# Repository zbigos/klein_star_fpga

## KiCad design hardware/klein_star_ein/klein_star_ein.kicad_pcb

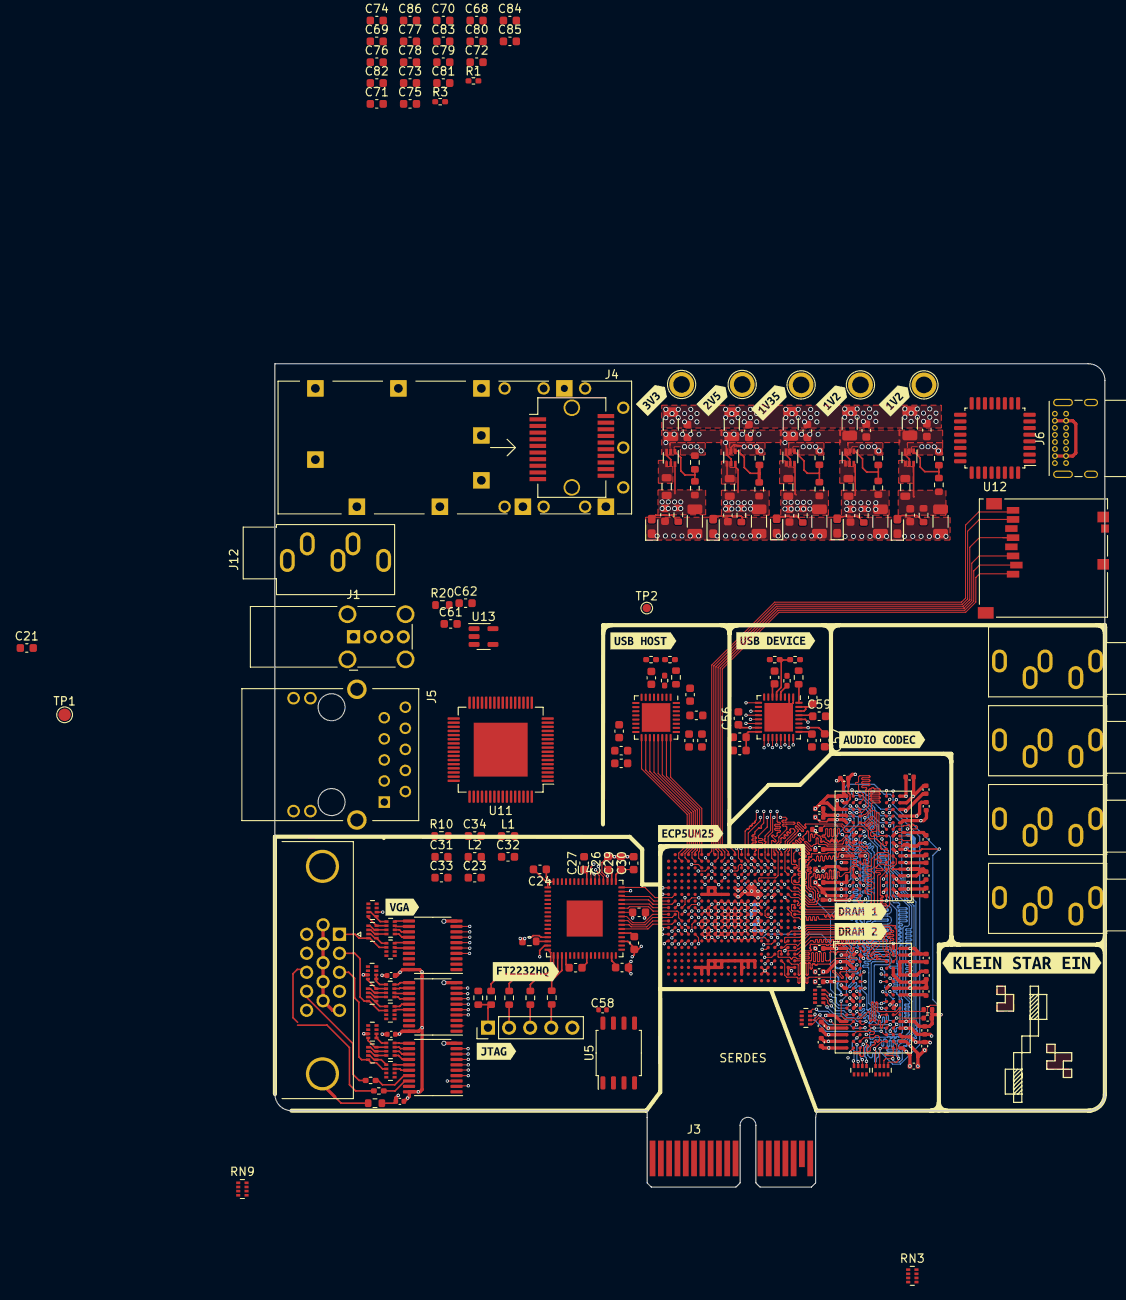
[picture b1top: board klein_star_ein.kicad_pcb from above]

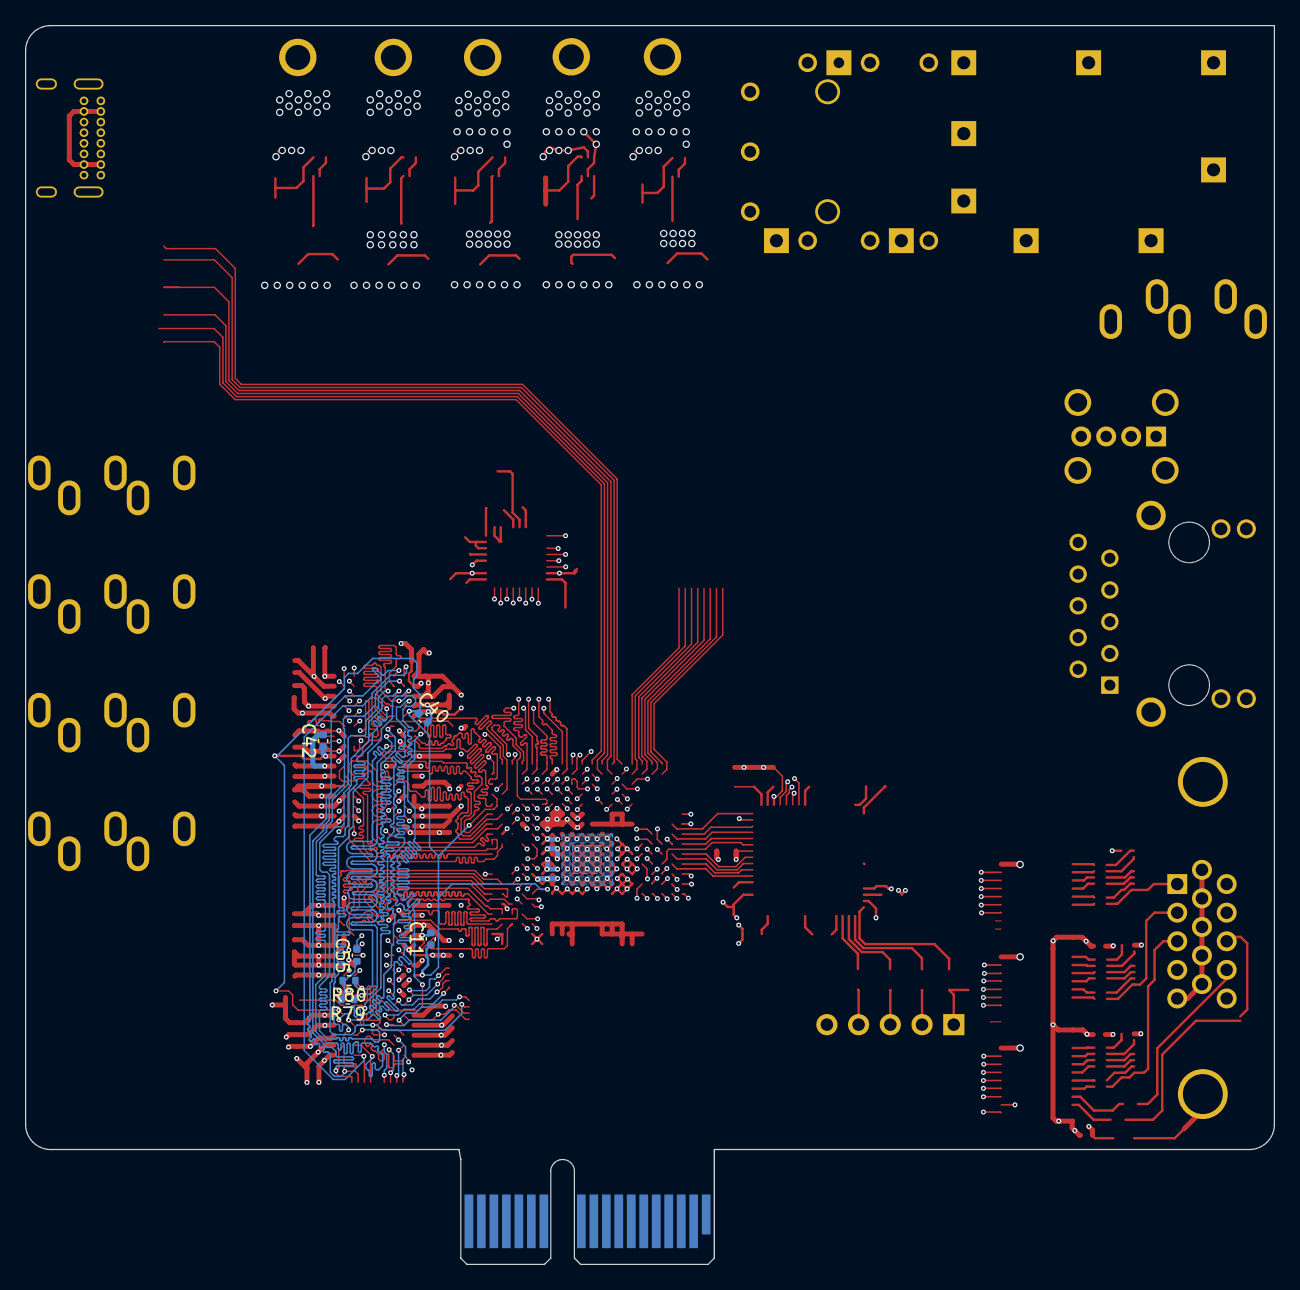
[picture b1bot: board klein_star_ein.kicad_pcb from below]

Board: 6 copper layers, 100.0 x 99.2 mm, 229 parts (6 on the bottom side), 252 nets.

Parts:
C1, C13: 4.7uF; C_0402_1005Metric
C2, C3, C4, C5, C6, C7, C8, C9, C10, C12, C14, C15, C16, C17, C18, C19, C20, C35, C36, C37, C38, C39, C58, C66: 470n; C_0402_1005Metric
C11, C40, C41, C42, C55: 100nF; C_0402_1005Metric
C21, C22, C23, C24, C25, C26, C27, C28, C29, C33, C34, C67: 100n; C_0603_1608Metric
C30, C31, C32, C61, C62: 4u7; C_0603_1608Metric
C43, C44, C45, C46, C47, C48, C49, C50, C51, C52, C53, C54, C56, C57, C59, C60: 100nF; C_0603_1608Metric
C63, C64, C65: 4u7; C_0402_1005Metric
C68, C69, C70, C71, C72, C73, C74, C75, C76, C77, C78, C79, C80, C81, C82, C83, C84, C85, C86: 0.1uF; C_0603_1608Metric
C87, C90, C91, C94, C95, C98, C99, C102, C103, C106: 22uF; C_1206_3216Metric
C88, C89, C92, C93, C96, C97, C100, C101, C104, C105: 22uF; C_0603_1608Metric
D1, D2, D3, D4, D5: LED; LED_0603_1608Metric_Pad1.05x0.95mm_HandSolder
J1: USB_A; USB_A_Wuerth_614004134726_Horizontal
J2: DB15_Female_HighDensity_MountingHoles; DSUB-15-HD_Male_Horizontal_P2.29x1.98mm_EdgePinOffset3.03mm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
J3: Bus_PCI_Express_x1; BUS_PCIexpress_x1
J4: 1367073-1; Connector_SFP_and_Cage
J5: ARJM11C7-502-AB-ER2-T; ABRACON_ARJM11C7-502-AB-ER2-T
J6: USB_C_Receptacle; USB_C_Receptacle_GCT_USB4085
J7: MEM2051-00-195-00-A
J8, J9, J10, J11, J12: AudioJack3_Ground_Switch; Jack_3.5mm_CUI_SJ1-3535NG_Horizontal
J13: Conn_01x05; PinHeader_1x05_P2.54mm_Vertical
L1, L2: L_Small; L_0603_1608Metric
L3, L4, L5, L6, L7: 1uH; L_0805_2012Metric
R1, R3: R220; R_0402_1005Metric_Pad0.72x0.64mm_HandSolder
R2, R5: 240R; R_0402_1005Metric
R4, R8, R14, R17, R21: 200k; R_0603_1608Metric
R6, R11, R15, R18, R22: 160k; R_0603_1608Metric
R7, R12, R16, R19, R23: R10; R_0603_1608Metric
R9, R20, R107: 10k; R_0603_1608Metric
R10: 12k +/-1%; R_0603_1608Metric
R13, R78: 12k 1%; R_0603_1608Metric
R26, R36: 1k; R_0402_1005Metric_Pad0.72x0.64mm_HandSolder
R29: 1M; R_0603_1608Metric
R44, R45: 100R; R_0402_1005Metric_Pad0.72x0.64mm_HandSolder
R76, R77, R105, R106: 0R; R_0402_1005Metric_Pad0.72x0.64mm_HandSolder
R79, R80: 51R; R_0402_1005Metric
R108, R109, R110, R111: 0R; R_0603_1608Metric
RN1, RN2, RN3, RN4, RN5, RN9, RN10, RN11, RN12, RN13, RN14, RN15, RN16, RN17, RN18, RN19, RN20, RN21: 51R; R_Array_Concave_4x0402
TP1: FTDI1V8REG; TestPoint_Pad_D1.5mm
TP2: 1V8; TestPoint_Pad_D1.0mm
TP3, TP4, TP5, TP6, TP7: TestPoint; TestPoint_Plated_Hole_D2.0mm
U1: ECP5UM25; Lattice_caBGA-381_17.0x17.0mm_Layout20x20_P0.8mm_Ball0.4mm_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
U2, U3: MT41K512M16; BGA-96_9.0x13.0mm_Layout2x3x16_P0.8mm
U4: FT2232HQ; QFN-64-1EP_9x9mm_P0.5mm_EP4.35x4.35mm
U5: W25Q128JVS; SOIC-8_5.23x5.23mm_P1.27mm
U6, U7: USB3300-EZK; QFN-32-1EP_5x5mm_P0.5mm_EP3.45x3.45mm
U8, U9, U10: SN74ALVC245PWR; TSSOP-20_4.4x6.5mm_P0.65mm
U11: KSZ9021RL; LQFP-64-1EP_10x10mm_P0.5mm_EP6.5x6.5mm
U12: TUSB2036; LQFP-32_7x7mm_P0.8mm
U13: TPS2041B; SOT-23-5
U14, U15, U16, U17, U18: AP61300Z6-7; SOT-563
kibuzzard-61F2DE20: G***; kibuzzard-61F2DE20
kibuzzard-61F2DE36: G***; kibuzzard-61F2DE36
kibuzzard-61F2DE40: G***; kibuzzard-61F2DE40
kibuzzard-61F2DEBF: G***; kibuzzard-61F2DEBF
kibuzzard-61F30A02: G***; kibuzzard-61F30A02
kibuzzard-61F30A12: G***; kibuzzard-61F30A12
kibuzzard-61F30A21: G***; kibuzzard-61F30A21
kibuzzard-61F31B82: G***; kibuzzard-61F31B82
kibuzzard-61F31C80: G***; kibuzzard-61F31C80
kibuzzard-61F32E72: G***; kibuzzard-61F32E72
kibuzzard-620E48A0: G***; kibuzzard-620E48A0
kibuzzard-620E48AE: G***; kibuzzard-620E48AE
kibuzzard-620E48DF, kibuzzard-620E48DF#2: G***; kibuzzard-620E48DF
kibuzzard-620E4897: G***; kibuzzard-620E4897

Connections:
1V35_DRAM_VCORE: C1.1, C2.1, C3.1, C4.1, C5.1, C6.1, C7.1, C8.1, C9.1, C10.1, C12.1, C13.1, C14.1, C15.1, C16.1, C17.1, C18.1, C19.1, C20.1, C35.1, C36.1, C37.1, C38.1, C39.1, C66.1, U1.F11 (VCCIO1/-), U1.F12 (VCCIO1/-), U1.H14 (VCCIO2/-), U1.H15 (VCCIO2/-), U1.J15 (VCCIO2/-), U1.L14 (VCCIO3/-), U1.L15 (VCCIO3/-), U1.M15 (VCCIO3/-), U2.A1 (Vddq), U2.A8 (Vddq), U2.B2 (Vdd), U2.C1 (Vddq), U2.C9 (Vddq), U2.D2 (Vddq), U2.D9 (Vdd), U2.E9 (Vddq), U2.F1 (Vddq), U2.G7 (Vdd), U2.H2 (Vddq), U2.H9 (Vddq), U2.K2 (Vdd), U2.K8 (Vdd), U2.N1 (Vdd), U2.N9 (Vdd), U2.R1 (Vdd), U2.R9 (Vdd), U3.A1 (Vddq), U3.A8 (Vddq), U3.B2 (Vdd), U3.C1 (Vddq), U3.C9 (Vddq), U3.D2 (Vddq), U3.D9 (Vdd), U3.E9 (Vddq), U3.F1 (Vddq), U3.G7 (Vdd), U3.H2 (Vddq), U3.H9 (Vddq), U3.K2 (Vdd), U3.K8 (Vdd), U3.N1 (Vdd), U3.N9 (Vdd), U3.R1 (Vdd), U3.R9 (Vdd)
5V_USB: J6.A4 (VBUS), J6.A9 (VBUS), J6.B4 (VBUS), J6.B9 (VBUS)
+1V2: C72.2, C73.1, C74.1, C75.1, C76.2, C81.2, C82.2, C83.1, C84.1, C85.1, C86.2, U11.4 (AVDDL), U11.5 (AVDDL), U11.12 (AVDDL), U11.13 (AVDDL), U11.22 (DVDDL), U11.29 (DVDDL), U11.35 (DVDDL), U11.40 (DVDDL), U11.52 (DVDDL), U11.54 (DVDDL), U11.58 (AVDD_PLL)
+1V8: C22.1, C23.1, C24.1, U4.12 (VCORE), U4.37 (VCORE), U4.64 (VCORE)
+3V3: C21.1, C25.1, C26.1, C27.1, C28.1, C43.1, C44.1, C45.1, C46.1, C47.1, C48.1, C49.1, C50.1, C51.1, C52.1, C58.1, C63.1, C64.1, C65.1, C67.1, C68.1, C69.1, C70.1, C71.2, C77.1, C78.1, C79.1, C80.2, L1.1, L2.1, R1.2, R3.1, R9.1, R76.2, R105.2, U1.L6 (VCCIO6/-), U1.L7 (VCCIO6/-), U1.M6 (VCCIO6/-), U4.20 (VCCIO), U4.31 (VCCIO), U4.42 (VCCIO), U4.50 (VREGIN), U4.56 (VCCIO), U5.8 (VCC), U6.6 (VDD3.3), U6.16 (VDD3.3), U6.25 (VDD3.3), U6.30 (VDD3.3), U6.31 (REG_EN), U7.6 (VDD3.3), U7.16 (VDD3.3), U7.25 (VDD3.3), U7.30 (VDD3.3), U7.31 (REG_EN), U8.20 (VCC), U9.20 (VCC), U10.20 (VCC), U11.6 (AVDDH), U11.16 (AVDDH), U11.20 (DVDDH), U11.30 (DVDDH), U11.37 (DVDDH), U11.44 (DVDDH), U11.61 (AVDDH), U11.64 (AVDDH)
+5V: C61.1, C87.1, C88.1, C91.1, C92.1, C95.1, C96.1, C99.1, C100.1, C103.1, C104.1, R36.1, U13.5 (IN), U14.3 (VIN), U14.5 (EN), U15.3 (VIN), U15.5 (EN), U16.3 (VIN), U16.5 (EN), U17.3 (VIN), U17.5 (EN), U18.3 (VIN), U18.5 (EN)
/1V2: C89.1, C90.1, L3.2, R4.1, R7.1, TP3.1, U14.6 (OUT)
/1V2_FPGA: C105.1, C106.1, L7.2, R21.1, R23.1, TP7.1, U18.6 (OUT)
/1V35: C93.1, C94.1, L4.2, R8.1, R12.1, TP4.1, U15.6 (OUT)
/2V5: C101.1, C102.1, L6.2, R17.1, R19.1, TP6.1, U17.6 (OUT)
/3V3: C97.1, C98.1, L5.2, R14.1, R16.1, TP5.1, U16.6 (OUT)
/DRAM_ADDR_0: RN5.6 (R3.2), U1.B17 (PT60A/-), U2.N3 (A0), U3.N3 (A0)
/DRAM_ADDR_1: U1.C13 (PT42B/-), U2.P7 (A1), U3.P7 (A1)
/DRAM_ADDR_2: RN1.8 (R1.2), U1.B16 (PT56B/-), U2.P3 (A2), U3.P3 (A2)
/DRAM_ADDR_3: RN5.8 (R1.2), U1.A17 (PT62A/-), U2.N2 (A3), U3.N2 (A3)
/DRAM_ADDR_4: U1.C14 (PT47B/-), U2.P8 (A4), U3.P8 (A4)
/DRAM_ADDR_5: U1.A16 (PT56A/-), U2.P2 (A5), U3.P2 (A5)
/DRAM_ADDR_6: RN2.5 (R4.2), U1.E11 (PT33B/PCLKC1_1), U2.R8 (A6), U3.R8 (A6)
/DRAM_ADDR_7: RN1.7 (R2.2), U1.A13 (PT40B/-), U2.R2 (A7), U3.R2 (A7)
/DRAM_ADDR_8: RN2.6 (R3.2), U1.C12 (PT35B/PCLKC1_0), U2.T8 (A8), U3.T8 (A8)
/DRAM_ADDR_9: RN1.5 (R4.2), U1.B15 (PT51A/-), U2.R3 (A9), U3.R3 (A9)
/DRAM_ADDR_10: U1.D16 (PT58B/-), U2.L7 (A10), U3.L7 (A10)
/DRAM_ADDR_11: RN2.8 (R1.2), U1.A18 (PT65A/-), U2.R7 (A11), U3.R7 (A11)
/DRAM_ADDR_12: U1.B20 (PT67B/-), U2.N7 (A12), U3.N7 (A12)
/DRAM_ADDR_13: RN1.6 (R3.2), U1.A14 (PT47A/-), U2.T3 (A13), U3.T3 (A13)
/DRAM_ADDR_14: RN2.7 (R2.2), U1.D11 (PT33A/PCLKT1_1), U2.T7 (A14), U3.T7 (A14)
/DRAM_ADDR_15: RN5.7 (R2.2), U1.C15 (PT51B/-), U2.M7 (A15), U3.M7 (A15)
/DRAM_ADDR_BA0: RN5.5 (R4.2), U1.A12 (PT40A/-), U2.M2 (BA0), U3.M2 (BA0)
/DRAM_ADDR_BA1: U1.E15 (PT53B/-), U2.N8 (BA1), U3.N8 (BA1)
/DRAM_ADDR_BA2: RN4.5 (R4.2), U1.B12 (PT35A/PCLKT1_0), U2.M3 (BA2), U3.M3 (BA2)
/DRAM_CKE: U1.D13 (PT44A/-), U2.K9 (CKE), U3.K9 (CKE)
/DRAM_CLK_N: R79.1, U1.E12 (PT38B/GR_PCLK1_1), U2.K7 (CK#), U3.K7 (CK#)
/DRAM_CLK_P: R80.1, U1.D12 (PT38A/GR_PCLK1_0), U2.J7 (CK), U3.J7 (CK)
/DRAM_DATA_0: U1.K20 (PR23D/RDQ20/PCLKC2_0), U2.E3 (DQ0)
/DRAM_DATA_1: U1.F20 (PR17C/RDQ20/-), U2.F7 (DQ1)
/DRAM_DATA_2: U1.J20 (PR23C/RDQ20/PCLKT2_0), U2.F2 (DQ2)
/DRAM_DATA_3: U1.F19 (PR17B/RDQ20/-), U2.F8 (DQ3)
/DRAM_DATA_4: U1.D19 (PR14B/RDQ20/-), U2.H3 (DQ4)
/DRAM_DATA_5: U1.E20 (PR17A/RDQ20/-), U2.H8 (DQ5)
/DRAM_DATA_6: U1.J19 (PR23A/RDQ20/PCLKT2_1), U2.G2 (DQ6)
/DRAM_DATA_7: U1.C20 (PR14A/RDQ20/-), U2.H7 (DQ7)
/DRAM_DATA_8: U1.E18 (PR5C/RDQ8/-), U2.D7 (DQ8)
/DRAM_DATA_9: U1.G16 (PR8C/RDQ8/-), U2.C3 (DQ9)
/DRAM_DATA_10: U1.F18 (PR5D/RDQ8/-), U2.C8 (DQ10)
/DRAM_DATA_11: U1.H16 (PR8D/RDQ8/-), U2.C2 (DQ11)
/DRAM_DATA_12: U1.F16 (PR2D/RDQ8/-), U2.A7 (DQ12)
/DRAM_DATA_13: U1.J17 (PR11C/RDQ8/-), U2.A2 (DQ13)
/DRAM_DATA_14: U1.E16 (PR2C/RDQ8/-), U2.B8 (DQ14)
/DRAM_DATA_15: U1.J16 (PR11D/RDQ8/-), U2.A3 (DQ15)
/DRAM_DATA_16: U1.N17 (PR35A/RDQ32/-), U3.E3 (DQ0)
/DRAM_DATA_17: U1.L17 (PR29B/RDQ32/-), U3.F7 (DQ1)
/DRAM_DATA_18: U1.R17 (PR35D/RDQ32/-), U3.F2 (DQ2)
/DRAM_DATA_19: U1.M18 (PR29D/RDQ32/-), U3.F8 (DQ3)
/DRAM_DATA_20: U1.P17 (PR32D/RDQ32/-), U3.H3 (DQ4)
/DRAM_DATA_21: U1.N18 (PR32C/RDQ32/-), U3.H8 (DQ5)
/DRAM_DATA_22: U1.R16 (PR35C/RDQ32/-), U3.G2 (DQ6)
/DRAM_DATA_23: U1.L16 (PR29A/RDQ32/GR_PCLK3_0), U3.H7 (DQ7)
/DRAM_DATA_24: U1.P20 (PR41A/RDQ44/-), U3.D7 (DQ8)
/DRAM_DATA_25: U1.U20 (PR41D/RDQ44/-), U3.C3 (DQ9)
/DRAM_DATA_26: U1.N19 (PR38A/RDQ44/-), U3.C8 (DQ10)
/DRAM_DATA_27: U1.U19 (PR44C/RDQ44/-), U3.C2 (DQ11)
/DRAM_DATA_28: U1.P19 (PR38C/RDQ44/-), U3.A7 (DQ12)
/DRAM_DATA_29: U1.T18 (PR44D/RDQ44/-), U3.A2 (DQ13)
/DRAM_DATA_30: U1.N20 (PR38B/RDQ44/-), U3.B8 (DQ14)
/DRAM_DATA_31: U1.T20 (PR41C/RDQ44/-), U3.A3 (DQ15)
/DRAM_DM0: U1.G20 (PR17D/RDQ20/-), U2.E7 (LDM)
/DRAM_DM1: U1.E17 (PR5B/RDQ8/-), U2.D3 (UDM)
/DRAM_DM2: U1.M20 (PR26B/RDQ32/PCLKC3_1), U3.E7 (LDM)
/DRAM_DM3: U1.U18 (PR47A/RDQ44/-), U3.D3 (UDM)
/DRAM_DQS0_N: U1.H20 (PR20B/RDQSN20/-), U2.G3 (LDQS#)
/DRAM_DQS0_P: U1.G19 (PR20A/RDQS20/GR_PCLK2_1), U2.F3 (LDQS)
/DRAM_DQS1_N: U1.G18 (PR8B/RDQSN8/-), U2.B7 (UDQS#)
/DRAM_DQS1_P: U1.F17 (PR8A/RDQS8/-), U2.C7 (UDQS)
/DRAM_DQS2_N: U1.M17 (PR32B/RDQSN32/-), U3.G3 (LDQS#)
/DRAM_DQS2_P: U1.N16 (PR32A/RDQS32/-), U3.F3 (LDQS)
/DRAM_DQS3_N: U1.R18 (PR44B/RDQSN44/-), U3.B7 (UDQS#)
/DRAM_DQS3_P: U1.T19 (PR44A/RDQS44/-), U3.C7 (UDQS)
/DRAM_ODT: RN4.8 (R1.2), U1.C17 (PT60B/-), U2.K1 (ODT), U3.K1 (ODT)
/DRAM_nCAS: U1.C16 (PT58A/-), U2.K3 (CAS#), U3.K3 (CAS#)
/DRAM_nCS: RN4.7 (R2.2), U1.D14 (PT49A/-), U2.L2 (CS#), U3.L2 (CS#)
/DRAM_nRAS: U1.D15 (PT53A/-), U2.J3 (RAS#), U3.J3 (RAS#)
/DRAM_nRESET: U1.B13 (PT42A/-), U2.T2 (RESET#), U3.T2 (RESET#)
/DRAM_nWE: RN4.6 (R3.2), U1.A19 (PT67A/-), U2.L3 (WE#), U3.L3 (WE#)
/FIFO_D0/RX: U1.L2 (PL41D/LDQ44/-), U4.38 (BDBUS0)
/FIFO_D1/TX: U1.L1 (PL44C/LDQ44/-), U4.39 (BDBUS1)
/FIFO_D2: U1.K2 (PL32A/LDQS32/-), U4.40 (BDBUS2)
/FIFO_D3: U1.K1 (PL32D/LDQ32/-), U4.41 (BDBUS3)
/FIFO_D4: U1.L3 (PL41C/LDQ44/-), U4.43 (BDBUS4)
/FIFO_D5: U1.J1 (PL32B/LDQSN32/-), U4.44 (BDBUS5)
/FIFO_D6: U1.H2 (PL26C/LDQ32/PCLKT6_0), U4.45 (BDBUS6)
/FIFO_D7: U1.H1 (PL32C/LDQ32/-), U4.46 (BDBUS7)
/FIFO_WKUP: U1.F1 (PL26B/LDQ32/PCLKC6_1), U4.55 (BCBUS4)
/FIFO_nRD: U1.J4 (PL29A/LDQ32/GR_PCLK6_0), U4.53 (BCBUS2)
/FIFO_nRXE: U1.G2 (PL26A/LDQ32/PCLKT6_1), U4.48 (BCBUS0)
/FIFO_nTXE: U1.G1 (PL26D/LDQ32/PCLKC6_0), U4.52 (BCBUS1)
/FIFO_nWR: U1.J3 (PL29C/LDQ32/GR_PCLK6_1), U4.54 (BCBUS3)
/FPGA_VCORE: U1.H8 (VCC/-), U1.H9 (VCC/-), U1.H10 (VCC/-), U1.H11 (VCC/-), U1.H12 (VCC/-), U1.H13 (VCC/-), U1.J8 (VCC/-), U1.J13 (VCC/-), U1.K8 (VCC/-), U1.K13 (VCC/-), U1.L8 (VCC/-), U1.L13 (VCC/-), U1.M8 (VCC/-), U1.M13 (VCC/-), U1.N8 (VCC/-), U1.N9 (VCC/-), U1.N10 (VCC/-), U1.N11 (VCC/-), U1.N12 (VCC/-), U1.N13 (VCC/-)
/JTAG_TCK: J13.1, R107.2, R108.2, U1.T5 (TCK/-)
/JTAG_TDI: J13.2, R109.2, U1.R5 (TDI/-)
/JTAG_TDO: J13.3, R110.2, U1.V4 (TDO/-)
/JTAG_TMS: J13.4, R111.2, U1.U5 (TMS/-)
/SD_CLK: J7.4 (CLK), U1.B8 (PT15B/-)
/SD_CMD: J7.6 (CMD), U1.A9 (PT24A/GR_PCLK0_1)
/SD_DATA0: J7.2 (DAT0), U1.A8 (PT18B/-)
/SD_DATA1: J7.1 (DAT1), U1.A7 (PT18A/-)
/SD_DATA2: J7.8 (DAT2), U1.A10 (PT27A/PCLKT0_1)
/SD_DATA3: J7.7 (CD/DAT3), U1.B9 (PT22A/-)
/SLAVE_EXTvBUS: U7.10 (EXTVBUS), U13.3 (~OC)
/USB_HOST_DATA0: U1.A6 (PT4A/-), U7.24 (DATA0)
/USB_HOST_DATA1: U1.B6 (PT4B/-), U7.23 (DATA1)
/USB_HOST_DATA2: U1.A5 (PL2B/LDQ8/-), U7.22 (DATA2)
/USB_HOST_DATA3: U1.B5 (PL2C/LDQ8/-), U7.21 (DATA3)
/USB_HOST_DATA4: U1.A4 (PL2A/LDQ8/-), U7.20 (DATA4)
/USB_HOST_DATA5: U1.B4 (PL5B/LDQ8/-), U7.19 (DATA5)
/USB_HOST_DATA6: U1.A3 (PL5C/LDQ8/-), U7.18 (DATA6)
/USB_HOST_DATA7: U1.B3 (PL5D/LDQ8/-), U7.17 (DATA7)
/USB_HOST_N: J1.2 (D-), U7.8 (DM)
/USB_HOST_P: J1.3 (D+), U7.7 (DP)
/USB_SLAVE_CLK: U1.A11 (PT27B/PCLKC0_1), U6.28 (XI)
/USB_SLAVE_CLKOUT: U1.C8 (PT15A/-), U6.14 (CLKOUT)
/USB_SLAVE_DATA0: U1.C11 (PT29B/PCLKC0_0), U6.24 (DATA0)
/USB_SLAVE_DATA1: U1.B11 (PT29A/PCLKT0_0), U6.23 (DATA1)
/USB_SLAVE_DATA2: U1.C10 (PT22B/-), U6.22 (DATA2)
/USB_SLAVE_DATA3: U1.B10 (PT24B/GR_PCLK0_0), U6.21 (DATA3)
/USB_SLAVE_DATA4: U1.E9 (PT20B/-), U6.20 (DATA4)
/USB_SLAVE_DATA5: U1.E8 (PT13A/-), U6.19 (DATA5)
/USB_SLAVE_DATA6: U1.E7 (PT9A/-), U6.18 (DATA6)
/USB_SLAVE_DATA7: U1.D8 (PT13B/-), U6.17 (DATA7)
/USB_SLAVE_DIR: U1.D7 (PT9B/-), U6.12 (DIR)
/USB_SLAVE_NXT: U1.C7 (PT11B/-), U6.11 (NXT)
/USB_SLAVE_RESET: U1.C6 (PT11A/-), U6.9 (RESET)
/USB_SLAVE_STP: U1.E6 (PT6A/-), U6.13 (STP)
/USB_SLAVE_vBUS: C62.1, J1.1 (VBUS), R26.1, U13.1 (OUT)
/VGA_AB: J2.3, RN12.8 (R1.2), RN13.6 (R3.2)
/VGA_AG: J2.2, RN15.6 (R3.2), RN16.8 (R1.2)
/VGA_AR: J2.1, RN19.6 (R3.2), RN20.8 (R1.2)
/VGA_BUF_B_0: RN19.3 (R3.1), U10.16 (B3)
/VGA_BUF_B_1: RN19.4 (R4.1), U10.15 (B4)
/VGA_BUF_B_2: RN18.1 (R1.1), U10.14 (B5)
/VGA_BUF_B_3: RN18.2 (R2.1), U10.13 (B6)
/VGA_BUF_B_4: RN18.3 (R3.1), U10.12 (B7)
/VGA_BUF_B_5: RN18.4 (R4.1), U10.11 (B8)
/VGA_BUF_G_0: RN15.3 (R3.1), U9.16 (B3)
/VGA_BUF_G_1: RN15.4 (R4.1), U9.15 (B4)
/VGA_BUF_G_2: RN14.1 (R1.1), U9.14 (B5)
/VGA_BUF_G_3: RN14.2 (R2.1), U9.13 (B6)
/VGA_BUF_G_4: RN14.3 (R3.1), U9.12 (B7)
/VGA_BUF_G_5: RN14.4 (R4.1), U9.11 (B8)
/VGA_BUF_HSYNC: R44.2, U8.18 (B1)
/VGA_BUF_R_0: RN13.3 (R3.1), U8.16 (B3)
/VGA_BUF_R_1: RN13.4 (R4.1), U8.15 (B4)
/VGA_BUF_R_2: RN11.1 (R1.1), U8.14 (B5)
/VGA_BUF_R_3: RN11.2 (R2.1), U8.13 (B6)
/VGA_BUF_R_4: RN11.3 (R3.1), U8.12 (B7)
/VGA_BUF_R_5: RN11.4 (R4.1), U8.11 (B8)
/VGA_BUF_VSYNC: R45.2, U8.17 (B2)
/VGA_B_1: U1.K3 (PL29D/LDQ32/-), U10.5 (A4)
/VGA_B_2: U1.L4 (PL35C/LDQ32/-), U10.6 (A5)
/VGA_B_3: U1.K4 (PL35A/LDQ32/-), U10.7 (A6)
/VGA_B_4: U1.K5 (PL35B/LDQ32/VREF1_6), U10.8 (A7)
/VGA_B_5: U1.J5 (PL29B/LDQ32/-), U10.9 (A8)
/VGA_G_0: U1.M1 (PL44B/LDQSN44/-), U9.4 (A3)
/VGA_G_1: U1.N3 (PL41A/LDQ44/-), U9.5 (A4)
/VGA_G_2: U1.N4 (PL38C/LDQ44/-), U9.6 (A5)
/VGA_G_3: U1.M3 (PL41B/LDQ44/-), U9.7 (A6)
/VGA_G_4: U1.M4 (PL38A/LDQ44/-), U9.8 (A7)
/VGA_G_5: U1.L5 (PL35D/LDQ32/-), U9.9 (A8)
/VGA_HSYNC: U1.N2 (PL44A/LDQS44/-), U8.2 (A1)
/VGA_R_0: U1.N5 (PL38B/LDQ44/-), U8.4 (A3)
/VGA_R_1: U1.P5 (PL38D/LDQ44/-), U8.5 (A4)
/VGA_R_2: U1.P4 (PL47D/LDQ44/LLC_GPLL0C_IN), U8.6 (A5)
/VGA_R_3: U1.P3 (PL47C/LDQ44/LLC_GPLL0T_IN), U8.7 (A6)
/VGA_R_4: U1.P2 (PL47B/LDQ44/-), U8.8 (A7)
/VGA_R_5: U1.P1 (PL47A/LDQ44/-), U8.9 (A8)
/VGA_VSYNC: U1.N1 (PL44D/LDQ44/-), U8.3 (A2)
DRAM_VREF: C11.1, C40.1, C41.1, C42.1, U1.D20 (PR14C/RDQ20/VREF1_2), U1.P16 (PR35B/RDQ32/VREF1_3), U2.H1 (Vrefdq), U2.M8 (Vrefca), U3.H1 (Vrefdq), U3.M8 (Vrefca)
GND: C1.2, C2.2, C3.2, C4.2, C5.2, C6.2, C7.2, C8.2, C9.2, C10.2, C11.2, C12.2, C13.2, C14.2, C15.2, C16.2, C17.2, C18.2, C19.2, C20.2, C21.2, C22.2, C23.2, C24.2, C25.2, C26.2, C27.2, C28.2, C29.2, C30.2, C31.2, C32.2, C33.2, C34.2, C35.2, C36.2, C37.2, C38.2, C39.2, C40.2, C41.2, C42.2, C43.2, C44.2, C45.2, C46.2, C47.2, C48.2, C49.2, C50.2, C51.2, C52.2, C53.2, C54.2, C55.2, C56.2, C57.2, C58.2, C59.2, C60.2, C61.2, C62.2, C63.2, C64.2, C65.2, C66.2, C67.2, C68.2, C69.2, C70.2, C71.1, C72.1, C73.2, C74.2, C75.2, C76.1, C77.2, C78.2, C79.2, C80.1, C81.1, C82.1, C83.2, C84.2, C85.2, C86.1, C87.2, C88.2, C89.2, C90.2, C91.2, C92.2, C93.2, C94.2, C95.2, C96.2, C97.2, C98.2, C99.2, C100.2, C101.2, C102.2, C103.2, C104.2, C105.2, C106.2, D1.1 (K), D2.1 (K), D3.1 (K), D4.1 (K), D5.1 (K), J1.4 (GND), J1.5 (Shield), J2.5, J2.6, J2.7, J2.8, J2.9, J2.10, J5.S1 (SHIELD), J5.S2 (SHIELD), J6.A1 (GND), J6.A12 (GND), J6.B1 (GND), J6.B12 (GND), J6.S1 (SHIELD), J7.3 (VSS), J13.5, R2.2, R5.2, R6.2, R10.1, R11.2, R13.1, R15.2, R18.2, R20.2, R22.2, R29.1, R77.2, R78.1, R106.2, R107.1, RN1.1 (R1.1), RN1.2 (R2.1), RN1.3 (R3.1), RN1.4 (R4.1), RN2.1 (R1.1), RN2.2 (R2.1), RN2.3 (R3.1), RN2.4 (R4.1), RN4.1 (R1.1), RN4.2 (R2.1), RN4.3 (R3.1), RN4.4 (R4.1), RN5.1 (R1.1), RN5.2 (R2.1), RN5.3 (R3.1), RN5.4 (R4.1), RN10.7 (R2.2), RN17.7 (R2.2), RN21.2 (R2.1), U1.B7 (GND/-), U1.B14 (GND/-), U1.C19 (GND/-), U1.D4 (GND/-), U1.F7 (GND/-), U1.F8 (GND/-), U1.F13 (GND/-), U1.F14 (GND/-), U1.G4 (GND/-), U1.G6 (GND/-), U1.G7 (GND/-), U1.G8 (GND/-), U1.G9 (GND/-), U1.G10 (GND/-), U1.G11 (GND/-), U1.G12 (GND/-), U1.G13 (GND/-), U1.G14 (GND/-), U1.G15 (GND/-), U1.G17 (GND/-), U1.H19 (GND/-), U1.J2 (GND/-), U1.J7 (GND/-), U1.J9 (GND/-), U1.J10 (GND/-), U1.J11 (GND/-), U1.J12 (GND/-), U1.J14 (GND/-), U1.K6 (GND/-), U1.K7 (GND/-), U1.K9 (GND/-), U1.K10 (GND/-), U1.K11 (GND/-), U1.K12 (GND/-), U1.K14 (GND/-), U1.K15 (GND/-), U1.L9 (GND/-), U1.L10 (GND/-), U1.L11 (GND/-), U1.L12 (GND/-), U1.M2 (GND/-), U1.M7 (GND/-), U1.M9 (GND/-), U1.M10 (GND/-), U1.M11 (GND/-), U1.M12 (GND/-), U1.M14 (GND/-), U1.M16 (GND/-), U1.N6 (GND/-), U1.N7 (GND/-), U1.N14 (GND/-), U1.N15 (GND/-), U1.P7 (GND/-), U1.P8 (GND/-), U1.P11 (GND/-), U1.P12 (GND/-), U1.P13 (GND/-), U1.P14 (GND/-), U1.R19 (GND/-), U1.U7 (GND/GND), U1.U8 (GND/GND), U1.U9 (GND/GND), U1.U10 (GND/GND), U1.U11 (GND/GND), U1.U12 (GND/GND), U1.U13 (GND/GND), U1.U14 (GND/GND), U1.V5 (GND/GND), U1.V6 (GND/GND), U1.V7 (GND/GND), U1.V8 (GND/GND), U1.V9 (GND/GND), U1.V12 (GND/GND), U1.V13 (GND/GND), U1.V14 (GND/GND), U1.V15 (GND/GND), U1.V16 (GND/GND), U1.V19 (GND/GND), U1.V20 (GND/GND), U1.W6 (GND/GND), U1.W7 (GND/GND), U1.W12 (GND/GND), U1.W15 (GND/GND), U1.W16 (GND/GND), U1.W19 (GND/GND), U2.A9 (Vss), U2.B1 (Vssq), U2.B3 (Vss), U2.B9 (Vssq), U2.D1 (Vssq), U2.D8 (Vssq), U2.E1 (Vss), U2.E2 (Vssq), U2.E8 (Vssq), U2.F9 (Vssq), U2.G1 (Vssq), U2.G8 (Vss), U2.G9 (Vssq), U2.J2 (Vss), U2.J8 (Vss), U2.M1 (Vss), U2.M9 (Vss), U2.P1 (Vss), U2.P9 (Vss), U2.T1 (Vss), U2.T9 (Vss), U3.A9 (Vss), U3.B1 (Vssq), U3.B3 (Vss), U3.B9 (Vssq), U3.D1 (Vssq), U3.D8 (Vssq), U3.E1 (Vss), U3.E2 (Vssq), U3.E8 (Vssq), U3.F9 (Vssq), U3.G1 (Vssq), U3.G8 (Vss), U3.G9 (Vssq), U3.J2 (Vss), U3.J8 (Vss), U3.M1 (Vss), U3.M9 (Vss), U3.P1 (Vss), U3.P9 (Vss), U3.T1 (Vss), U3.T9 (Vss), U4.1 (GND), U4.5 (GND), U4.10 (AGND), U4.11 (GND), U4.13 (TEST), U4.15 (GND), U4.25 (GND), U4.35 (GND), U4.47 (GND), U4.51 (GND), U4.65 (GND), U5.4 (GND), U6.1 (GND), U6.2 (GND), U6.33 (GND), U7.1 (GND), U7.2 (GND), U7.33 (GND), U8.10 (GND), U9.10 (GND), U10.10 (GND), U11.3 (AGNDH), U11.9 (AGNDH), U11.17 (VSS), U11.18 (VSS), U11.23 (VSS), U11.28 (VSS), U11.34 (VSS), U11.39 (VSS), U11.53 (VSS), U11.63 (AGNDH_BG), U11.65 (EP), U13.2 (GND), U14.2 (GND), U15.2 (GND), U16.2 (GND), U17.2 (GND), U18.2 (GND)
unnamed: C29.1, C30.1, TP1.1, U4.49 (VREGOUT)
unnamed: C31.1, C32.1, L2.2, U4.4 (VPHY)
unnamed: C33.1, C34.1, L1.2, U4.9 (VPLL)
unnamed: C53.1, C54.1, TP2.1, U7.15 (VDD1.8), U7.26 (VDD1.8)
unnamed: C55.1, R79.2, R80.2
unnamed: C56.1, C57.1, U6.15 (VDD1.8), U6.26 (VDD1.8)
unnamed: C59.1, U6.29 (VDDA1.8)
unnamed: C60.1, U7.29 (VDDA1.8)
unnamed: D1.2 (A), R7.2
unnamed: D2.2 (A), R12.2
unnamed: D3.2 (A), R16.2
unnamed: D4.2 (A), R19.2
unnamed: D5.2 (A), R23.2
unnamed: J2.0, R29.2
unnamed: J2.13, R44.1
unnamed: J2.14, R45.1
unnamed: J3.A2 (+12V), J3.A3 (+12V), J3.B1 (+12V), J3.B2 (+12V), J3.B3 (+12V)
unnamed: J3.A9 (+3.3V), J3.A10 (+3.3V), J3.B8 (+3.3V)
unnamed: J3.A4 (GND), J3.A12 (GND), J3.A15 (GND), J3.A18 (GND), J3.B4 (GND), J3.B7 (GND), J3.B13 (GND), J3.B16 (GND), J3.B18 (GND)
unnamed: J5.1 (TRD1+), U11.1 (TXRXP_A)
unnamed: J5.2 (TRD1-), U11.2 (TXRXM_A)
unnamed: J5.3 (TRD2+), U11.7 (TXRXP_B)
unnamed: J5.4 (TRD2-), U11.8 (TXRXM_B)
unnamed: J5.7 (TRD3+), U11.10 (TXRXP_C)
unnamed: J5.8 (TRD3-), U11.11 (TXRXM_C)
unnamed: J5.9 (TRD4+), U11.14 (TXRXP_D)
unnamed: J5.10 (TRD4-), U11.15 (TXRXM_D)
unnamed: J5.L1 (LED-L_A_GRN), R1.1
unnamed: J5.L2 (LED-L_K_GRN), U11.19 (LED2/PHYAD1)
unnamed: J5.L3 (LED-R_A_YLW), R3.2
unnamed: J5.L4 (LED-R_K_YLW), U11.21 (LED1/PHYAD0)
unnamed: J6.A6 (D+), J6.B6 (D+), U12.1 (DP0)
unnamed: J6.A7 (D-), J6.B7 (D-), U12.2 (DM0)
unnamed: L3.1, U14.4 (SW)
unnamed: L4.1, U15.4 (SW)
unnamed: L5.1, U16.4 (SW)
unnamed: L6.1, U17.4 (SW)
unnamed: L7.1, U18.4 (SW)
unnamed: R2.1, U2.L8 (ZQ)
unnamed: R4.2, R6.1, U14.1 (FB)
unnamed: R5.1, U3.L8 (ZQ)
unnamed: R9.2, U4.14 (~RESET)
unnamed: R10.2, U4.6 (REF)
unnamed: R8.2, R11.1, U15.1 (FB)
unnamed: R13.2, U6.32 (RBIAS)
unnamed: R14.2, R15.1, U16.1 (FB)
unnamed: R17.2, R18.1, U17.1 (FB)
unnamed: R20.1, U13.4 (~EN)
unnamed: R21.2, R22.1, U18.1 (FB)
unnamed: R26.2, U7.4 (VBUS)
unnamed: R36.2, U6.4 (VBUS)
unnamed: R76.1, R77.1, U7.5 (ID)
unnamed: R78.2, U7.32 (RBIAS)
unnamed: R105.1, R106.1, U6.5 (ID)
unnamed: R108.1, U4.16 (ADBUS0)
unnamed: R109.1, U4.17 (ADBUS1)
unnamed: R110.1, U4.18 (ADBUS2)
unnamed: R111.1, U4.19 (ADBUS3)
unnamed: RN10.1 (R1.1), RN10.2 (R2.1), RN11.5 (R4.2)
unnamed: RN10.8 (R1.2), RN11.6 (R3.2), RN12.4 (R4.1)
unnamed: RN11.7 (R2.2), RN12.3 (R3.1), RN12.5 (R4.2)
unnamed: RN11.8 (R1.2), RN12.2 (R2.1), RN12.6 (R3.2)
unnamed: RN12.1 (R1.1), RN12.7 (R2.2), RN13.5 (R4.2)
unnamed: RN14.5 (R4.2), RN17.1 (R1.1), RN17.2 (R2.1)
unnamed: RN14.6 (R3.2), RN16.4 (R4.1), RN17.8 (R1.2)
unnamed: RN14.7 (R2.2), RN16.3 (R3.1), RN16.5 (R4.2)
unnamed: RN14.8 (R1.2), RN16.2 (R2.1), RN16.6 (R3.2)
unnamed: RN15.5 (R4.2), RN16.1 (R1.1), RN16.7 (R2.2)
unnamed: RN18.5 (R4.2), RN21.1 (R1.1), RN21.7 (R2.2)
unnamed: RN18.6 (R3.2), RN20.4 (R4.1), RN21.8 (R1.2)
unnamed: RN18.7 (R2.2), RN20.3 (R3.1), RN20.5 (R4.2)
unnamed: RN18.8 (R1.2), RN20.2 (R2.1), RN20.6 (R3.2)
unnamed: RN19.5 (R4.2), RN20.1 (R1.1), RN20.7 (R2.2)
USB_FPGA_N: U6.8 (DM), U12.19 (DM3)
USB_FPGA_P: U6.7 (DP), U12.20 (DP3)

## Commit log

2021-10-30 initial with MT41K512M16 symbol
2021-11-05 initial footprint parser for banks 0+1
2021-11-10 banks 2 3 6 7 with DQgroup support
2021-11-10 added SERDES gen and piggibacked SWD on it
2021-11-10 added a really shitty power pin generation
2021-11-21 Added submodules for litex and linux-on-litex
2021-11-21 Added submodules required by litex
2021-11-21 Added git lfs management for archive files
2021-11-22 fixed DRAM, added initial schematic
2021-11-24 Added riscv toolchain under tools
2021-12-02 Added pre-commit configuration
2021-12-02 Applied fixes from pre-commit to all files
2021-12-05 Added autopep8 to commit hooks
2021-12-05 Formated all python files
2022-01-04 no idea what's here
2022-01-04 Added gitignore, removed unnecessary files
2022-01-04 Fixed paths to custom symbols
2022-01-04 Added AP61300Z6-7 symbol
2022-01-04 Added KSZ9021RL symbol
2022-01-04 Removed local cache file
2022-01-05 Added MEM2051-00-195-00-A symbol and footprint
2022-01-05 Readded MEM_2051-00-195-00-A symbol
2022-01-05 Added PUSB3FR6Z symbol and footprint
2022-01-05 Added SN74ALVC245PWR symbol and footprint
2022-01-05 Added 1367073-1 symbol and footprint
2022-01-07 changed RAM symbol, schematic of FT, USB PHY and VGA. Rerouted DRAM
2022-01-07 remove backup
2022-01-07 Delete MT41K512M16.bak
    Local file, KiCad artifact
2022-01-07 Delete fp-info-cache
    Local file, KiCad artifact
2022-01-07 Delete classes.cpython-38.pyc
    Local file, python artifact
2022-01-07 Delete symbolgen.cpython-38.pyc
    Local file, python artifact
2022-01-08 review
2022-01-08 fixes
    Aligned pins to grid, hid the footprint field
2022-01-08 fixed
    redone entire thing
2022-01-08 review
    fixed minor things, renumbered pads on footprint
2022-01-08 fixes
    There already is a SFP-with-cage footprint,
    redone symbol with https://www.mouser.com/catalog/specsheets/elx10gdl0610710elt_ka.pdf in mind, changed footprint to existing one, removed previous
2022-01-08 Removed second unit of KSZ9021RL and selected power input pins
2022-01-08 VGA phy schematic and layout
2022-01-09 power failure
2022-01-13 changed VGA drivers to use resistor networks
2022-01-23 a
    a
2022-01-24 dram layout
2022-01-26 bus matching script
2022-01-26 what the fuck
2022-01-26 Added decups to KSZ9021
2022-01-27 Switched decupling caps to bigger size
2022-01-27 Prototype of power section footprint
2022-02-01 rzeczy
2022-02-03 Implmented power sections as hierarchical sheet
2022-02-03 Sync pcb file

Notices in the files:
parts and their libraries:
Copyright 2021 Accelerated Designs. All rights reserved.
